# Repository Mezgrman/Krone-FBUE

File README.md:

# What's this?
See my [pyFIS](https://github.com/Mezgrman/pyFIS) repo.

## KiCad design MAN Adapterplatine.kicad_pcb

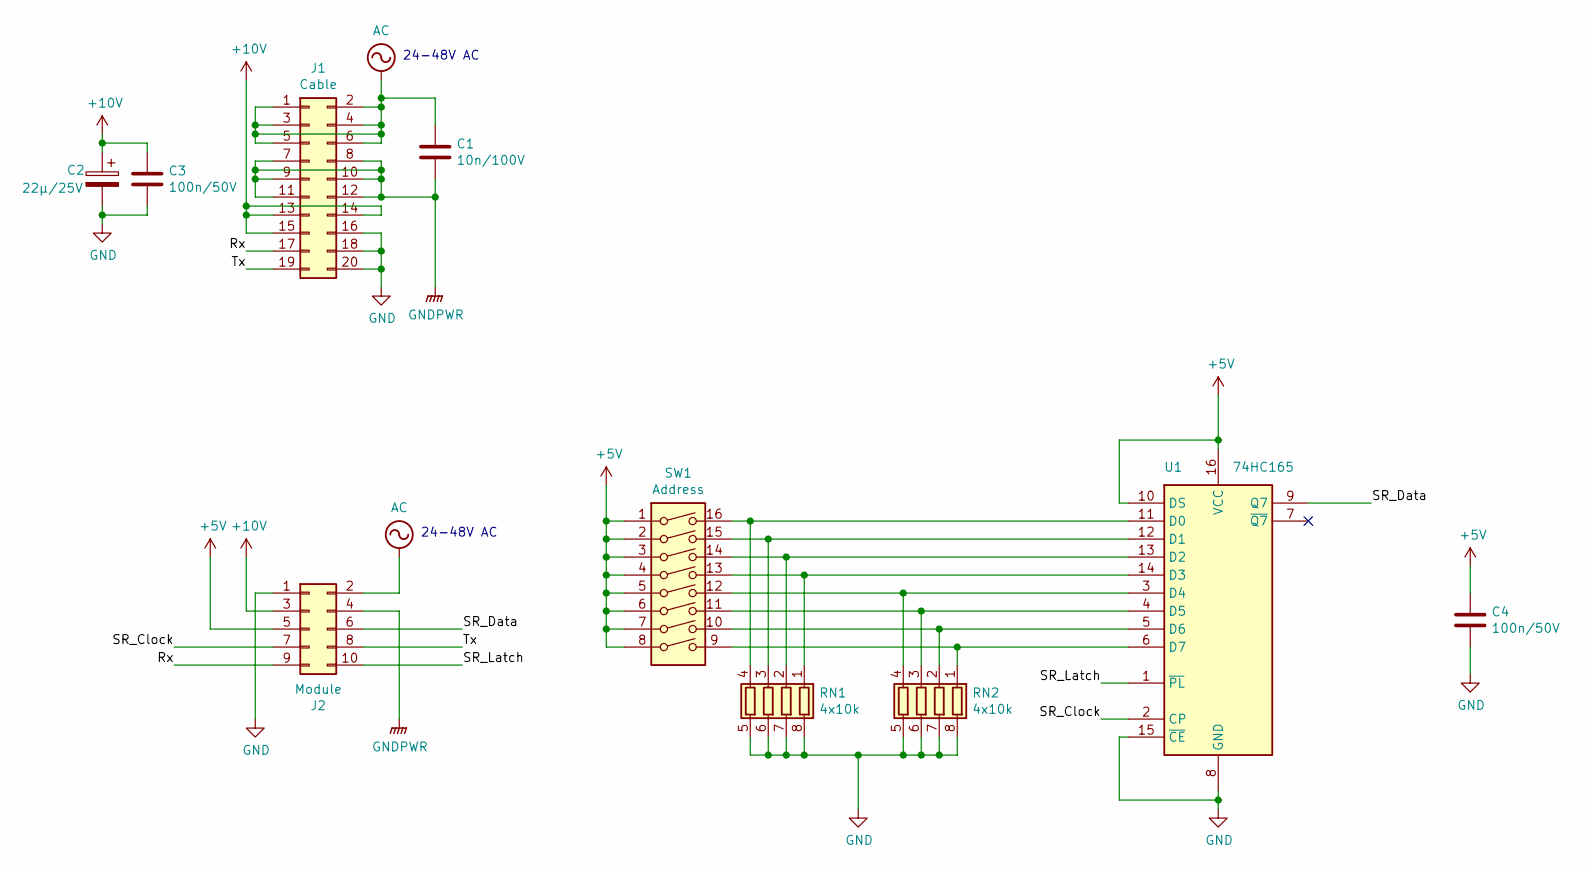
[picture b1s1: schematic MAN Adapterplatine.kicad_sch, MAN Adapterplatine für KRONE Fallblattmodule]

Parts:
C1: 10n/100V; C_0805
C2: 22µ/25V; CP_Tantalum_Case-D_EIA-7343-31_Reflow
C3, C4: 100n/50V; C_0603
J1: Cable; IDC_Header_Straight_20pins
J2: Module; Pin_Header_Straight_2x05
RN1, RN2: 4x10k; R_Array_Convex_4x0603
SW1: Address; SW_DIP_x8_Slide_SolderJumpers
U1: 74HC165; SOIC-16_3.9x9.9mm_Pitch1.27mm

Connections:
+5V: C4.1, J2.5, SW1.1, SW1.2, SW1.3, SW1.4, SW1.5, SW1.6, SW1.7, SW1.8, U1.10 (DS), U1.16 (VCC)
+10V: C2.1, C3.1, J1.13, J1.14, J1.15, J2.3
/Rx: J1.17, J2.9
/SR_Clock: J2.7, U1.2 (CP)
/SR_Data: J2.6, U1.9 (Q7)
/SR_Latch: J2.10, U1.1 (~PL)
/Tx: J1.19, J2.8
AC: C1.1, J1.1, J1.2, J1.3, J1.4, J1.5, J1.6, J2.2
GND: C2.2, C3.2, C4.2, J1.16, J1.18, J1.20, J2.1, RN1.5 (R4.2), RN1.6 (R3.2), RN1.7 (R2.2), RN1.8 (R1.2), RN2.5 (R4.2), RN2.6 (R3.2), RN2.7 (R2.2), RN2.8 (R1.2), U1.8 (GND), U1.15 (~CE)
GNDPWR: C1.2, J1.7, J1.8, J1.9, J1.10, J1.11, J1.12, J2.4
unnamed: RN1.1 (R1.1), SW1.13, U1.14 (D3)
unnamed: RN1.2 (R2.1), SW1.14, U1.13 (D2)
unnamed: RN1.3 (R3.1), SW1.15, U1.12 (D1)
unnamed: RN1.4 (R4.1), SW1.16, U1.11 (D0)
unnamed: RN2.1 (R1.1), SW1.9, U1.6 (D7)
unnamed: RN2.2 (R2.1), SW1.10, U1.5 (D6)
unnamed: RN2.3 (R3.1), SW1.11, U1.4 (D5)
unnamed: RN2.4 (R4.1), SW1.12, U1.3 (D4)

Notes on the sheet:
24-48V AC

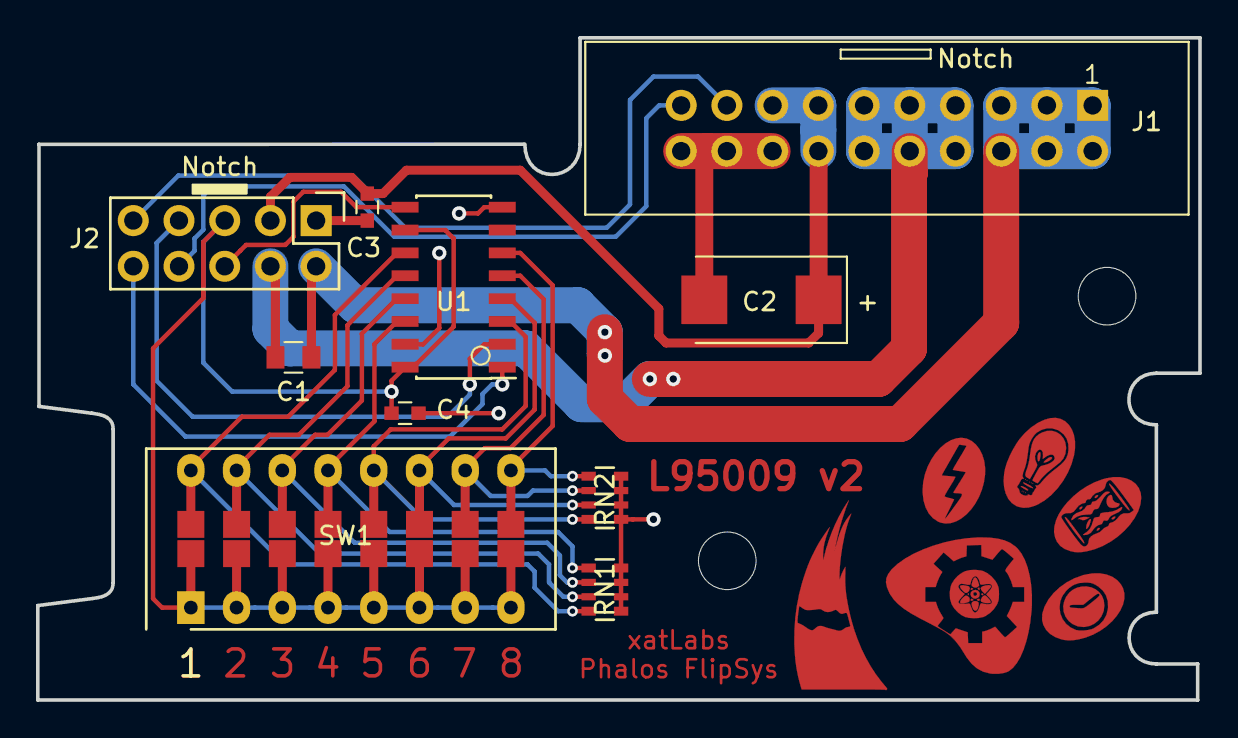
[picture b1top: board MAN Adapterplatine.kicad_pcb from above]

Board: 2 copper layers, 64.6 x 36.8 mm, 10 parts (0 on the bottom side), 18 nets.

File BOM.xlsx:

Item | Qty | Reference(s) | Value | Order No. | Supplier
1 | 1 | C1 | 10n/100V | CL21B103KCANNNC | TME
2 | 1 | C2 | 22Âµ/25V | T491D226M025AT | TME
3 | 2 | C3,C4 | 100n/50V | VJ0603Y104KXACW1BC | TME
4 | 1 | J1 | Cable | T821-1-20-S1 | TME
5 | 1 | J2 | Module | ZL262-10DG | TME
6 | 2 | RN2,RN1 | 4x10k | YC164-JR-0710K | TME
7 | 1 | SW1 | Address | EAH108E | TME
8 | 1 | U1 | 74HC165 | 74HC165D.653 | TME

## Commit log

2019-10-24 Updated readme and gitignore
2020-09-12 Update README (pySplitFlap => pyFIS)
2020-12-01 Add schematic PDF
2021-12-04 Change DIP switch to include solder jumpers, add Elecrow data
2021-12-09 Unspecified changes
